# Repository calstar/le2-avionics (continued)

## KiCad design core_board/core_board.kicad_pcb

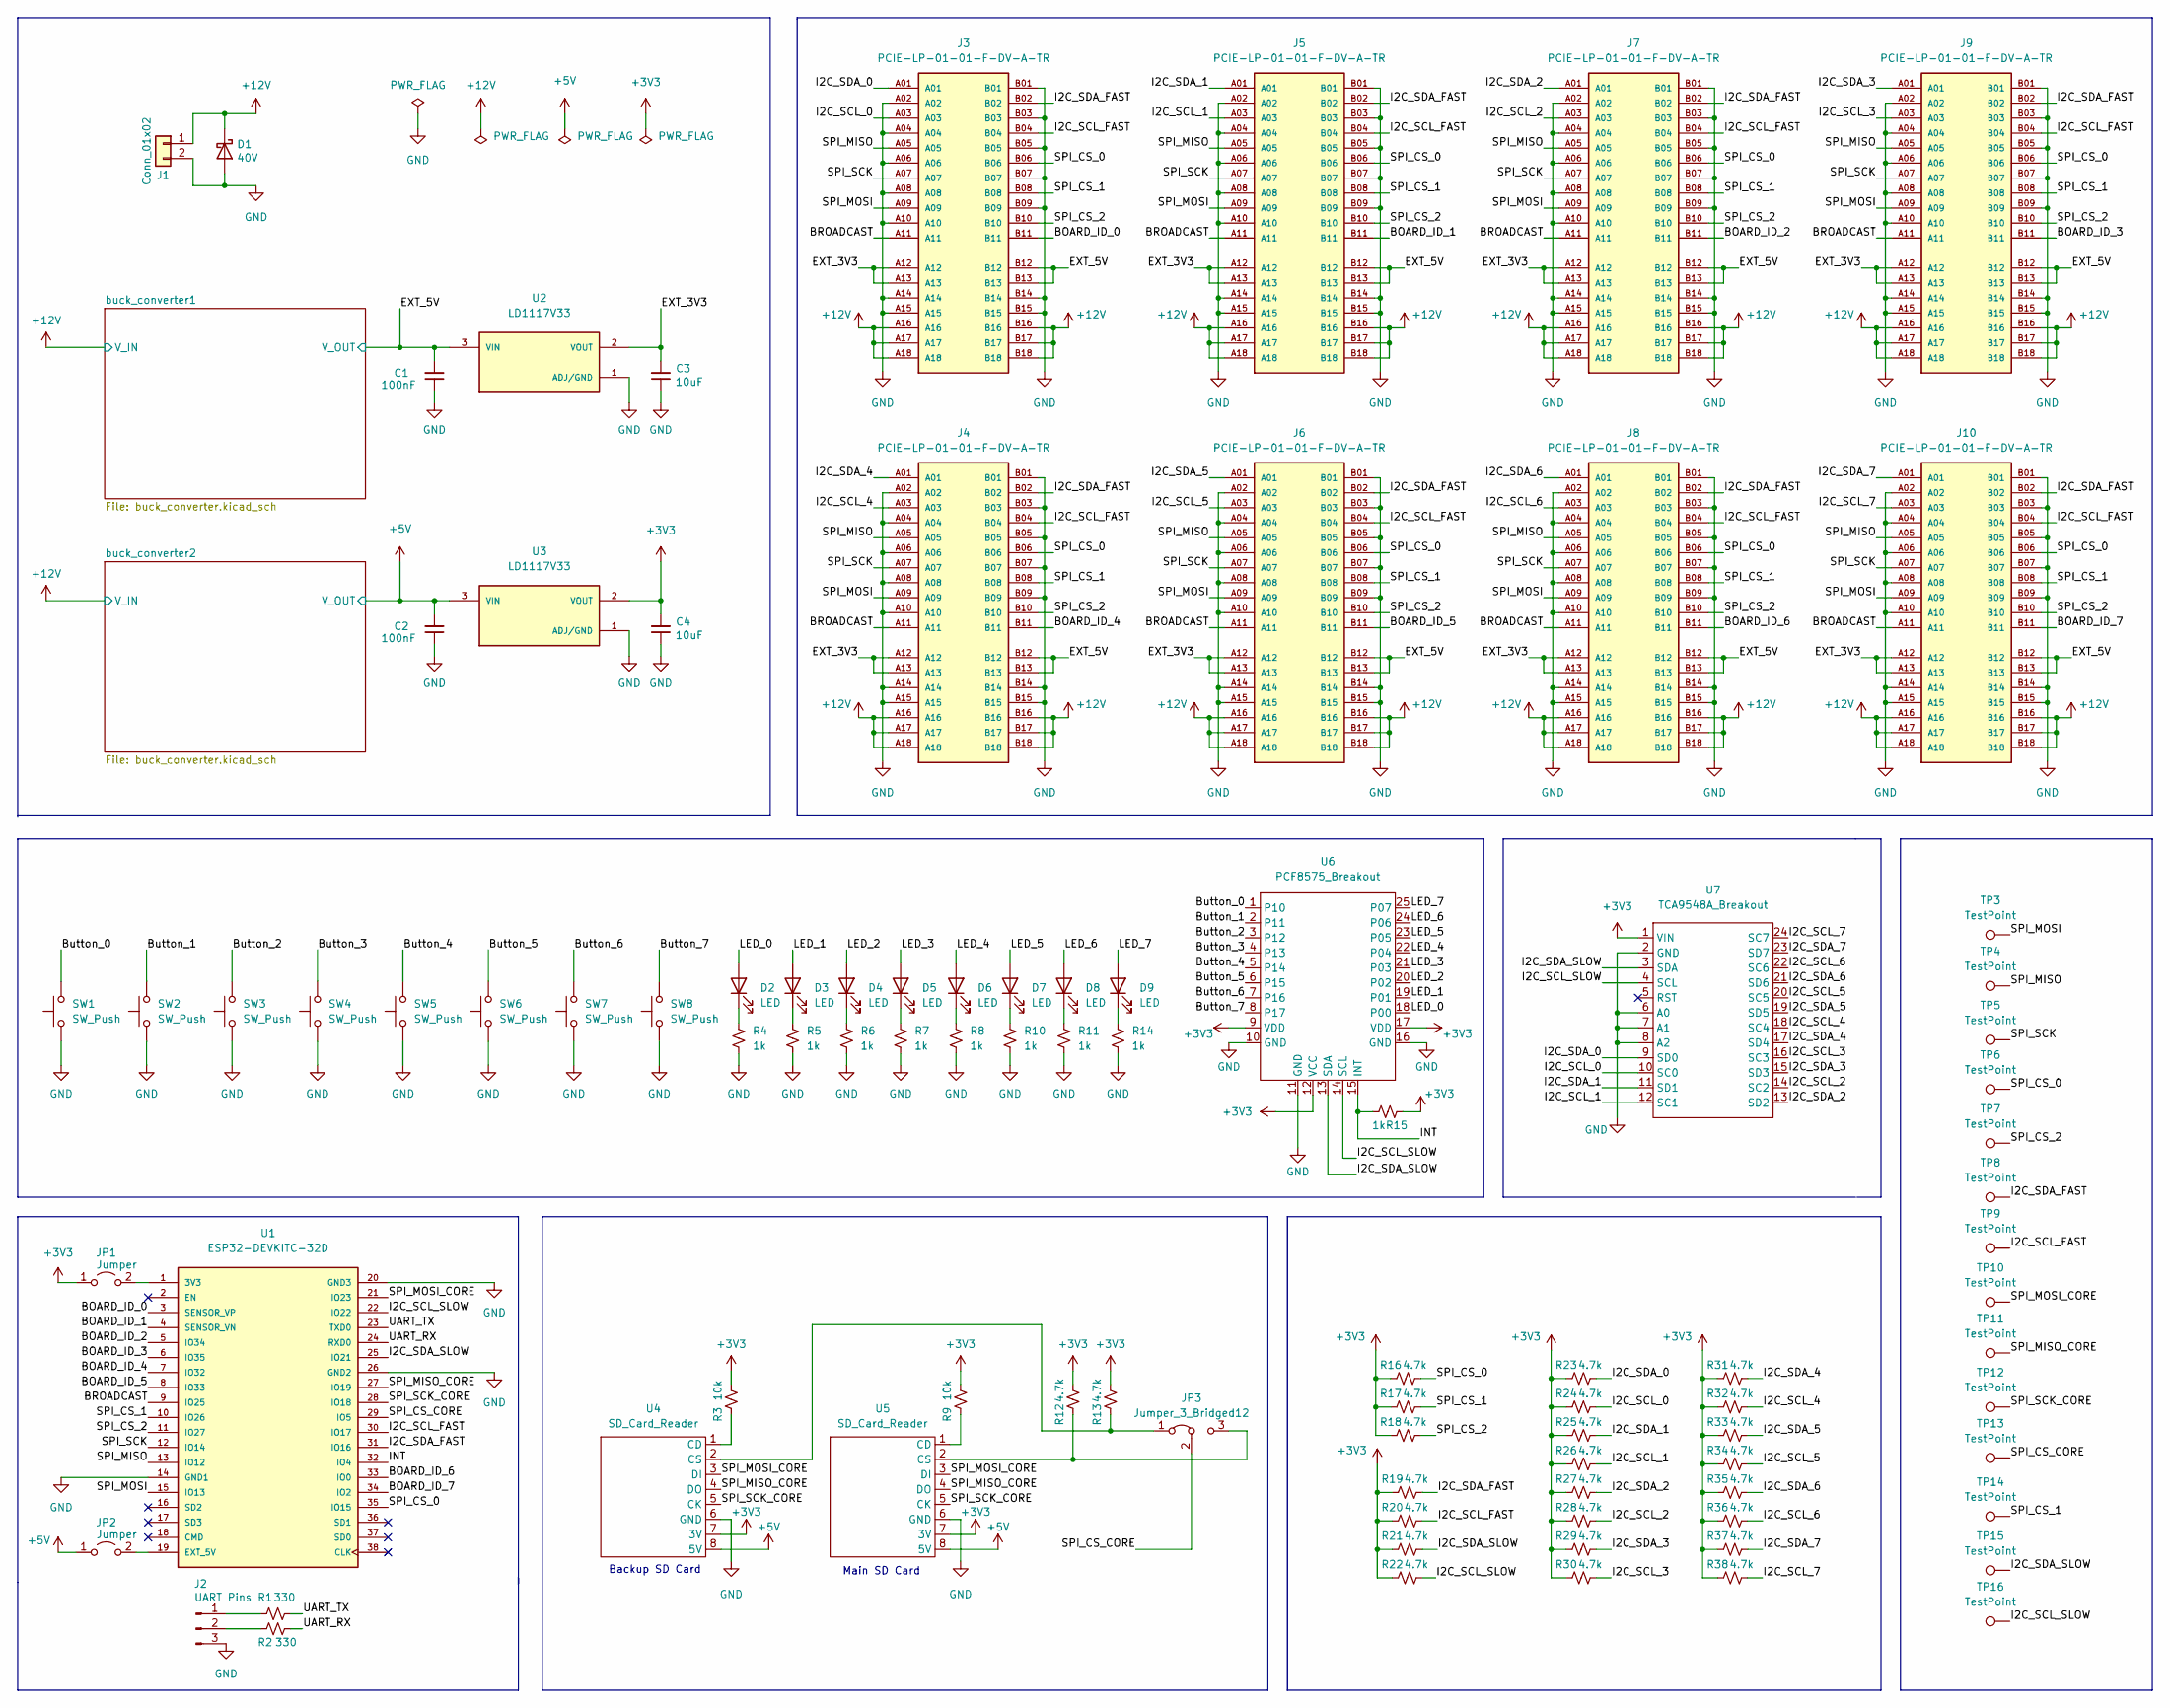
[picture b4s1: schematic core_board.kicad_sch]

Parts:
C1, C2: 100nF; C_0603_1608Metric
C3, C4: 10uF; C_0603_1608Metric
D1: 40V; D_0603_1608Metric; DIGIKEY 478-7798-1-ND
D2, D3, D4, D5, D6, D7, D8, D9: LED; LED_0603_1608Metric
J1: Conn_01x02; DEANS
J2: UART Pins; PinHeader_1x03_P2.54mm_Vertical
J3, J4, J5, J6, J7, J8, J9, J10: PCIE-LP-01-01-F-DV-A-TR; SAMTEC_PCIE-LP-01-01-F-DV-A-TR; PARTREV B
JP1, JP2: Jumper; PinHeader_1x02_P2.54mm_Vertical
JP3: Jumper_3_Bridged12; PinHeader_1x03_P2.54mm_Vertical
R1, R2: 330; R_0603_1608Metric
R3, R9: 10k; R_0603_1608Metric
R4, R5, R6, R7, R8, R10, R11, R14, R15: 1k; R_0603_1608Metric
R12, R13, R16, R17, R18, R19, R20, R21, R22, R23, R24, R25, R26, R27, R28, R29, R30, R31, R32, R33, R34, R35, R36, R37, R38: 4.7k; R_0603_1608Metric
SW1, SW2, SW3, SW4, SW5, SW6, SW7, SW8: SW_Push; SW_SPST_PTS810
TP3, TP4, TP5, TP6, TP7, TP8, TP9, TP10, TP11, TP12, TP13, TP14, TP15, TP16: TestPoint; TestPoint_Plated_Hole_D2.0mm
U1: ESP32-DEVKITC-32D; MODULE_ESP32-DEVKITC-32D; PARTREV 4
U2, U3: LD1117V33; TO255P1020X450X1968-3; PARTREV 37
U4, U5: SD_Card_Reader; SD_Card_Breakout
U6: PCF8575_Breakout
U7: TCA9548A_Breakout

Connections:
+3V3: C4.2, JP1.1 (A), R3.2, R9.2, R12.2, R13.2, R15.1, R16.1, R17.1, R18.1, R19.1, R20.1, R21.1, R22.1, R23.1, R24.1, R25.1, R26.1, R27.1, R28.1, R29.1, R30.1, R31.1, R32.1, R33.1, R34.1, R35.1, R36.1, R37.1, R38.1, U3.2 (VOUT), U4.7 (3V), U5.7 (3V), U6.9 (VDD), U6.12 (VCC), U6.17 (VDD), U7.1 (VIN)
+5V: C2.2, JP2.1 (A), U3.3 (VIN), U4.8 (5V), U5.8 (5V); also elsewhere on the board
+12V: D1.1 (K), J1.1, J3.A16, J3.A17, J3.A18, J3.B16, J3.B17, J3.B18, J4.A16, J4.A17, J4.A18, J4.B16, J4.B17, J4.B18, J5.A16, J5.A17, J5.A18, J5.B16, J5.B17, J5.B18, J6.A16, J6.A17, J6.A18, J6.B16, J6.B17, J6.B18, J7.A16, J7.A17, J7.A18, J7.B16, J7.B17, J7.B18, J8.A16, J8.A17, J8.A18, J8.B16, J8.B17, J8.B18, J9.A16, J9.A17, J9.A18, J9.B16, J9.B17, J9.B18, J10.A16, J10.A17, J10.A18, J10.B16, J10.B17, J10.B18; also elsewhere on the board
/BOARD_ID_0: J3.B11, U1.3 (SENSOR_VP)
/BOARD_ID_1: J5.B11, U1.4 (SENSOR_VN)
/BOARD_ID_2: J7.B11, U1.5 (IO34)
/BOARD_ID_3: J9.B11, U1.6 (IO35)
/BOARD_ID_4: J4.B11, U1.7 (IO32)
/BOARD_ID_5: J6.B11, U1.8 (IO33)
/BOARD_ID_6: J8.B11, U1.33 (IO0)
/BOARD_ID_7: J10.B11, U1.34 (IO2)
/BROADCAST: J3.A11, J4.A11, J5.A11, J6.A11, J7.A11, J8.A11, J9.A11, J10.A11, U1.9 (IO25)
/Button_0: SW1.2, U6.1 (P10)
/Button_1: SW2.2, U6.2 (P11)
/Button_2: SW3.2, U6.3 (P12)
/Button_3: SW4.2, U6.4 (P13)
/Button_4: SW5.2, U6.5 (P14)
/Button_5: SW6.2, U6.6 (P15)
/Button_6: SW7.2, U6.7 (P16)
/Button_7: SW8.2, U6.8 (P17)
/EXT_3V3: C3.2, J3.A12, J3.A13, J4.A12, J4.A13, J5.A12, J5.A13, J6.A12, J6.A13, J7.A12, J7.A13, J8.A12, J8.A13, J9.A12, J9.A13, J10.A12, J10.A13, U2.2 (VOUT)
/EXT_5V: C1.2, J3.B12, J3.B13, J4.B12, J4.B13, J5.B12, J5.B13, J6.B12, J6.B13, J7.B12, J7.B13, J8.B12, J8.B13, J9.B12, J9.B13, J10.B12, J10.B13, U2.3 (VIN); also elsewhere on the board
/I2C_SCL_0: J3.A03, R24.2, U7.10 (SC0)
/I2C_SCL_1: J5.A03, R26.2, U7.12 (SC1)
/I2C_SCL_2: J7.A03, R28.2, U7.14 (SC2)
/I2C_SCL_3: J9.A03, R30.2, U7.16 (SC3)
/I2C_SCL_4: J4.A03, R32.2, U7.18 (SC4)
/I2C_SCL_5: J6.A03, R34.2, U7.20 (SC5)
/I2C_SCL_6: J8.A03, R36.2, U7.22 (SC6)
/I2C_SCL_7: J10.A03, R38.2, U7.24 (SC7)
/I2C_SCL_FAST: J3.B04, J4.B04, J5.B04, J6.B04, J7.B04, J8.B04, J9.B04, J10.B04, R20.2, TP9.1, U1.30 (IO17)
/I2C_SCL_SLOW: R22.2, TP16.1, U1.22 (IO22), U6.14 (SCL), U7.4 (SCL)
/I2C_SDA_0: J3.A01, R23.2, U7.9 (SD0)
/I2C_SDA_1: J5.A01, R25.2, U7.11 (SD1)
/I2C_SDA_2: J7.A01, R27.2, U7.13 (SD2)
/I2C_SDA_3: J9.A01, R29.2, U7.15 (SD3)
/I2C_SDA_4: J4.A01, R31.2, U7.17 (SD4)
/I2C_SDA_5: J6.A01, R33.2, U7.19 (SD5)
/I2C_SDA_6: J8.A01, R35.2, U7.21 (SD6)
/I2C_SDA_7: J10.A01, R37.2, U7.23 (SD7)
/I2C_SDA_FAST: J3.B02, J4.B02, J5.B02, J6.B02, J7.B02, J8.B02, J9.B02, J10.B02, R19.2, TP8.1, U1.31 (IO16)
/I2C_SDA_SLOW: R21.2, TP15.1, U1.25 (IO21), U6.13 (SDA), U7.3 (SDA)
/INT: R15.2, U1.32 (IO4), U6.15 (INT)
/LED_0: D2.2 (A), U6.18 (P00)
/LED_1: D3.2 (A), U6.19 (P01)
/LED_2: D4.2 (A), U6.20 (P02)
/LED_3: D5.2 (A), U6.21 (P03)
/LED_4: D6.2 (A), U6.22 (P04)
/LED_5: D7.2 (A), U6.23 (P05)
/LED_6: D8.2 (A), U6.24 (P06)
/LED_7: D9.2 (A), U6.25 (P07)
/SPI_CS_0: J3.B06, J4.B06, J5.B06, J6.B06, J7.B06, J8.B06, J9.B06, J10.B06, R16.2, TP6.1, U1.35 (IO15)
/SPI_CS_1: J3.B08, J4.B08, J5.B08, J6.B08, J7.B08, J8.B08, J9.B08, J10.B08, R17.2, TP14.1, U1.10 (IO26)
/SPI_CS_2: J3.B10, J4.B10, J5.B10, J6.B10, J7.B10, J8.B10, J9.B10, J10.B10, R18.2, TP7.1, U1.11 (IO27)
/SPI_CS_CORE: JP3.2 (C), TP13.1, U1.29 (IO5)
/SPI_MISO: J3.A05, J4.A05, J5.A05, J6.A05, J7.A05, J8.A05, J9.A05, J10.A05, TP4.1, U1.13 (IO12)
/SPI_MISO_CORE: TP11.1, U1.27 (IO19), U4.4 (DO), U5.4 (DO)
/SPI_MOSI: J3.A09, J4.A09, J5.A09, J6.A09, J7.A09, J8.A09, J9.A09, J10.A09, TP3.1, U1.15 (IO13)
/SPI_MOSI_CORE: TP10.1, U1.21 (IO23), U4.3 (DI), U5.3 (DI)
/SPI_SCK: J3.A07, J4.A07, J5.A07, J6.A07, J7.A07, J8.A07, J9.A07, J10.A07, TP5.1, U1.12 (IO14)
/SPI_SCK_CORE: TP12.1, U1.28 (IO18), U4.5 (CK), U5.5 (CK)
/UART_RX: R2.2, U1.24 (RXD0)
/UART_TX: R1.2, U1.23 (TXD0)
GND: C1.1, C2.1, C3.1, C4.1, D1.2 (A), J1.2, J2.3, J3.A02, J3.A04, J3.A06, J3.A08, J3.A10, J3.A14, J3.A15, J3.B01, J3.B03, J3.B05, J3.B07, J3.B09, J3.B14, J3.B15, J4.A02, J4.A04, J4.A06, J4.A08, J4.A10, J4.A14, J4.A15, J4.B01, J4.B03, J4.B05, J4.B07, J4.B09, J4.B14, J4.B15, J5.A02, J5.A04, J5.A06, J5.A08, J5.A10, J5.A14, J5.A15, J5.B01, J5.B03, J5.B05, J5.B07, J5.B09, J5.B14, J5.B15, J6.A02, J6.A04, J6.A06, J6.A08, J6.A10, J6.A14, J6.A15, J6.B01, J6.B03, J6.B05, J6.B07, J6.B09, J6.B14, J6.B15, J7.A02, J7.A04, J7.A06, J7.A08, J7.A10, J7.A14, J7.A15, J7.B01, J7.B03, J7.B05, J7.B07, J7.B09, J7.B14, J7.B15, J8.A02, J8.A04, J8.A06, J8.A08, J8.A10, J8.A14, J8.A15, J8.B01, J8.B03, J8.B05, J8.B07, J8.B09, J8.B14, J8.B15, J9.A02, J9.A04, J9.A06, J9.A08, J9.A10, J9.A14, J9.A15, J9.B01, J9.B03, J9.B05, J9.B07, J9.B09, J9.B14, J9.B15, J10.A02, J10.A04, J10.A06, J10.A08, J10.A10, J10.A14, J10.A15, J10.B01, J10.B03, J10.B05, J10.B07, J10.B09, J10.B14, J10.B15, R4.2, R5.2, R6.2, R7.2, R8.2, R10.2, R11.2, R14.2, SW1.1, SW2.1, SW3.1, SW4.1, SW5.1, SW6.1, SW7.1, SW8.1, U1.14 (GND1), U1.20 (GND3), U1.26 (GND2), U2.1 (ADJ/GND), U3.1 (ADJ/GND), U4.6 (GND), U5.6 (GND), U6.10 (GND), U6.11 (GND), U6.16 (GND), U7.2 (GND), U7.6 (A0), U7.7 (A1), U7.8 (A2); also elsewhere on the board
unnamed: D2.1 (K), R4.1
unnamed: D3.1 (K), R5.1
unnamed: D4.1 (K), R6.1
unnamed: D5.1 (K), R7.1
unnamed: D6.1 (K), R8.1
unnamed: D7.1 (K), R10.1
unnamed: D8.1 (K), R11.1
unnamed: D9.1 (K), R14.1
unnamed: J2.1, R1.1
unnamed: J2.2, R2.1
unnamed: JP1.2 (B), U1.1 (3V3)
unnamed: JP2.2 (B), U1.19 (EXT_5V)
unnamed: JP3.1 (A), R13.1, U4.2 (CS)
unnamed: JP3.3 (B), R12.1, U5.2 (CS)
unnamed: R3.1, U4.1 (CD)
unnamed: R9.1, U5.1 (CD)

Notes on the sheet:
Main SD Card
Backup SD Card

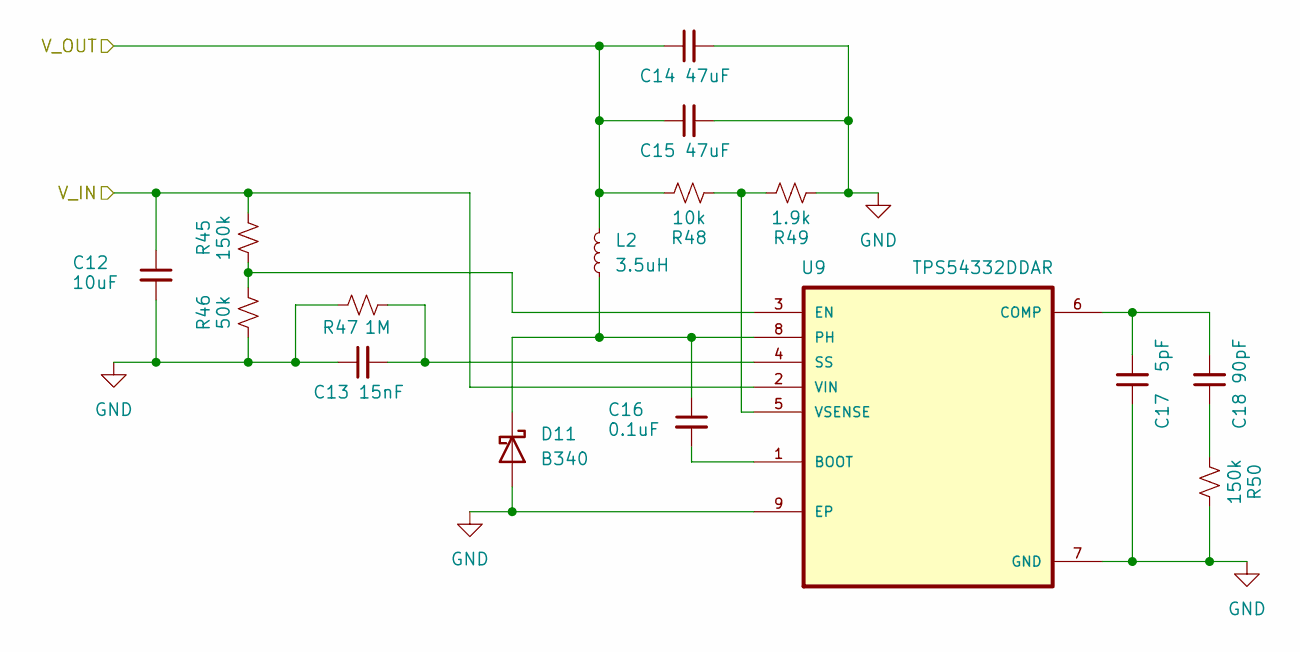
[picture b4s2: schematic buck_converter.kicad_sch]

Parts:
C12: 10uF; C_0603_1608Metric
C13: 15nF; C_0603_1608Metric
C14, C15: 47uF; C_1206_3216Metric
C16: 0.1uF; C_0603_1608Metric
C17: 5pF; C_0603_1608Metric
C18: 90pF; C_0603_1608Metric
D11: B340; D_SMC
L2: 3.5uH; L_Bourns_SRP5030T
R45, R50: 150k; R_0603_1608Metric
R46: 50k; R_0603_1608Metric
R47: 1M; R_0603_1608Metric
R48: 10k; R_0603_1608Metric
R49: 1.9k; R_0603_1608Metric
U9: TPS54332DDAR; VREG_LM5017MR_NOPB

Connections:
+5V: C14.1, C15.1, L2.2, R48.2; also elsewhere on the board
+12V: C12.1, R45.2, U9.2 (VIN); also elsewhere on the board
GND: C12.2, C13.1, C14.2, C15.2, C17.1, D11.2 (A), R46.1, R47.1, R49.1, R50.2, U9.7 (GND), U9.9 (EP); also elsewhere on the board
unnamed: C13.2, R47.2, U9.4 (SS)
unnamed: C16.1, D11.1 (K), L2.1, U9.8 (PH)
unnamed: C16.2, U9.1 (BOOT)
unnamed: C17.2, C18.2, U9.6 (COMP)
unnamed: C18.1, R50.1
unnamed: R45.1, R46.2, U9.3 (EN)
unnamed: R48.1, R49.2, U9.5 (VSENSE)

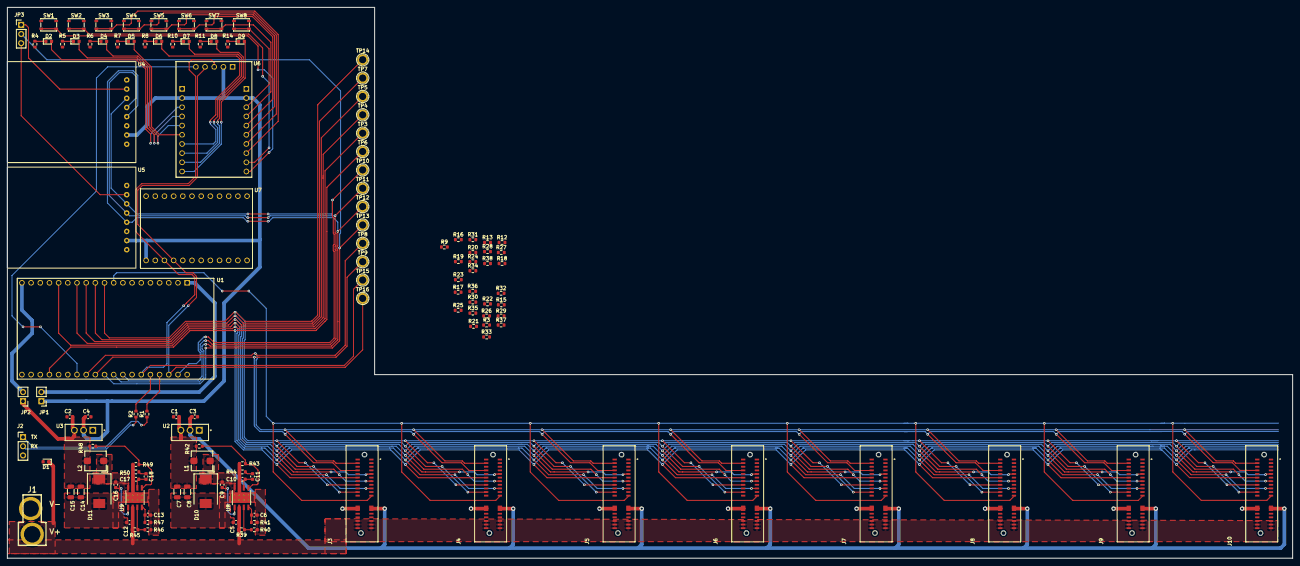
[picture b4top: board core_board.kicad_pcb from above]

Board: 2 copper layers, 355.6 x 152.4 mm, 125 parts (0 on the bottom side), 94 nets.

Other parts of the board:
C5: 10uF; C_0603_1608Metric
C6: 15nF; C_0603_1608Metric
C7, C8: 47uF; C_1206_3216Metric
C9: 0.1uF; C_0603_1608Metric
C10: 5pF; C_0603_1608Metric
C11: 90pF; C_0603_1608Metric
D10: B340; D_SMC
L1: 3.5uH; L_Bourns_SRP5030T
R39, R44: 150k; R_0603_1608Metric
R40: 50k; R_0603_1608Metric
R41: 1M; R_0603_1608Metric
R42: 10k; R_0603_1608Metric
R43: 1.9k; R_0603_1608Metric
U8: TPS54332DDAR; VREG_LM5017MR_NOPB

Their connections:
+12V: C5.1, R39.2, U8.2 (VIN); also elsewhere on the board
/EXT_5V: C7.1, C8.1, L1.2, R42.2; also elsewhere on the board
GND: C5.2, C6.1, C7.2, C8.2, C10.1, D10.2 (A), R40.1, R41.1, R43.1, R44.2, U8.7 (GND), U8.9 (EP); also elsewhere on the board
unnamed: C6.2, R41.2, U8.4 (SS)
unnamed: C9.1, D10.1 (K), L1.1, U8.8 (PH)
unnamed: C9.2, U8.1 (BOOT)
unnamed: C10.2, C11.2, U8.6 (COMP)
unnamed: C11.1, R44.1
unnamed: R39.1, R40.2, U8.3 (EN)
unnamed: R42.1, R43.2, U8.5 (VSENSE)

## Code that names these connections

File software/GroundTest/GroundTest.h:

#include <Arduino.h>
#include <Wire.h>
#include <SPI.h>
#include <FS.h>
#include <SD.h>

/* Library: https://www.arduino.cc/reference/en/libraries/tca9548a/ */
#include <TCA9548A.h>

/* Library: https://www.arduino.cc/reference/en/libraries/pcf8575/ */
#include <PCF8575.h>

/* Value that can be checked in other files so that this file isn't included twice. */
#define GROUND_TEST_HEADER_FILE_INCLUDED true

#define PIN_I2C_SLOW_SDA 21
#define PIN_I2C_SLOW_SCL 22

#define PIN_I2C_FAST_SDA 16
#define PIN_I2C_FAST_SCL 17

#define PIN_SPI_MISO 12
#define PIN_SPI_MOSI 13
#define PIN_SPI_SCK 14
#define PIN_SPI_CS_0 15
#define PIN_SPI_CS_1 26
#define PIN_SPI_CS_2 27

#define PIN_SPI_MISO_CORE 19
#define PIN_SPI_MOSI_CORE 23
#define PIN_SPI_SCK_CORE 18
#define PIN_SPI_CS_CORE 5

#define PIN_BOARD_ID_0 36
#define PIN_BOARD_ID_1 39
#define PIN_BOARD_ID_2 34
#define PIN_BOARD_ID_3 35
#define PIN_BOARD_ID_4 32
#define PIN_BOARD_ID_5 33
#define PIN_BOARD_ID_6 0
#define PIN_BOARD_ID_7 2

#define PIN_BROADCAST 25

#define PIN_IO_EXPANDER_INTERRUPT 4

#define BOARD_ID_IGNITER      493
#define BOARD_ID_SOLENOID     1127
#define BOARD_ID_SERVO        1253
#define BOARD_ID_THERMOCOUPLE 1761
#define BOARD_ID_RTD          2385
#define BOARD_ID_PT           3024

#define I2C_MUX_ADDRESS 0x70
#define CORE_IO_EXPANDER_ADDRESS 0x20

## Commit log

2022-09-13 igniter schematic work in progress
2022-09-13 igniter wip
2022-09-18 Started on Core Board schematic
2022-09-23 small updates
2022-09-24 Added link to hardware-sch-block
2022-09-26 finished schematic
2022-09-26 updated to 15-pin dsub
2022-09-28 Init branch
2022-09-30 Revised schematic based on Trevor's plan
2022-10-01 incorporated changed from design review meeting
2022-10-02 added LDO
2022-10-02 small changes
2022-10-02 added PCIE connectors
2022-10-07 Modified footprint assignment
2022-10-08 updating number of PTs on pt + lc board
2022-10-08 board to sensor connections
2022-10-08 adding I2C expander
2022-10-08 d-sub pin assignment rtds
2022-10-09 more RTD changes
2022-10-09 cleaning up
2022-10-09 removing accidentally added folder
2022-10-09 removing accidentally added files
2022-10-09 storing changes
2022-10-09 updating pin assignment + symbols
2022-10-12 updates to connector
2022-10-13 last commit before starting layout
2022-10-13 created netlist
2022-10-14 did layout, and power routing
2022-10-15 more routing progress
2022-10-15 more routing
2022-10-16 finished layout and routing
2022-10-17 minor edits
2022-10-17 minor changes
2022-10-21 small edits to power supply
2022-10-23 added screw terminals
2022-10-26 Started on thermocouple board.
2022-10-27 mounting holes
2022-10-28 minor edit
2022-10-28 remove hardware-sch-blocks
2022-10-28 submodule add
2022-10-28 small change to core
2022-10-30 Almost done with layout. Need board-to-board connection.
2022-10-30 Mostly finished with board.
2022-11-01 more mounting holes the more the merrier
2022-11-01 Updated board_ID.
2022-11-01 changed shape of core board
2022-11-01 Finished thermocouple board.
2022-11-01 updates to layout + board settings, not complete yet
2022-11-02 minor updates
2022-11-02 finishing up traces
2022-11-02 Adjusted card edge position.
2022-11-02 Fixing errors in thermocouple_board.
2022-11-03 adding board id resistors + silkscreen labels
2022-11-04 moved UART pins
2022-11-04 updated gerbers for core board
2022-11-08 added sldprt files for board specs first draft
2022-11-15 started on software
2022-11-18 updates to le2 software
2022-11-18 remove old files
2022-11-19 mostly finished with CoreBoard software
2022-11-23 code for IO Expander works now
2022-11-23 IO Expander code fixed, added more code
2022-11-23 wrote code to test igniter board
2022-11-24 added code for RTD board
2022-11-24 wrote code for PT Board
2022-11-25 added SD card code
2022-11-26 updated thermocouple board code
2022-11-27 added buttons-and-leds testing file
2022-11-27 rtd circuit sim
2022-11-28 wstone sim successfulgit add inst_opamp_sim
2022-11-29 added TestPT and TestIgniter
2022-12-16 igniter board code works
2022-12-17 more work on PT board code
2023-01-10 relay_board new pcb
2023-01-10 relay board new
